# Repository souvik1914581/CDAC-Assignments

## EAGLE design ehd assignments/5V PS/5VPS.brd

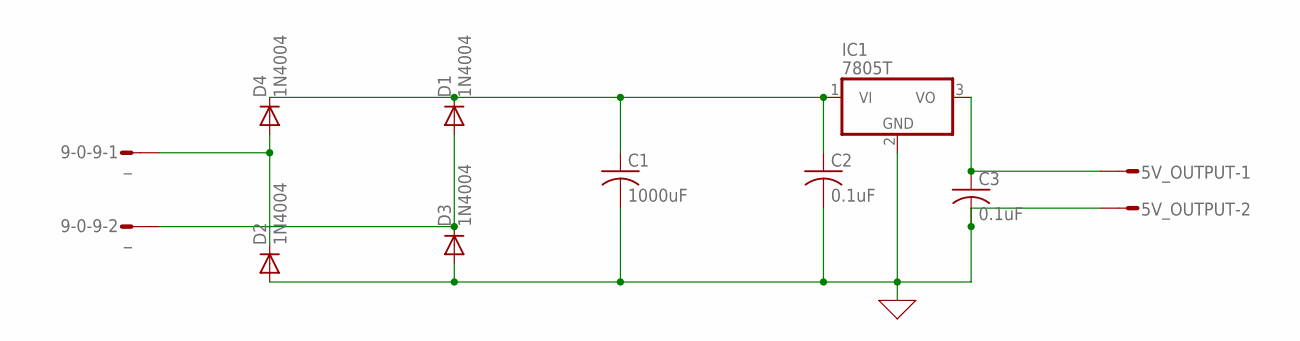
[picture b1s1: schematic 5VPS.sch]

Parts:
5V_OUTPUT: L02P
9-0-9: _; L02P
C1: 1000uF; C025-030X050
C2, C3: 0.1uF; C025-024X044
D1, D2, D3, D4: 1N4004; DO41-10
IC1: 7805T; TO220H

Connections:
0: 5V_OUTPUT.2, C1.2, C2.2, C3.2, D2.A, D3.A, IC1.2 (GND)
unnamed: 9-0-9.1, D2.C, D4.A
unnamed: C1.1, C2.1, D1.C, D4.C, IC1.1 (VI)
unnamed: 5V_OUTPUT.1, C3.1, IC1.3 (VO)
unnamed: 9-0-9.2, D1.A, D3.C

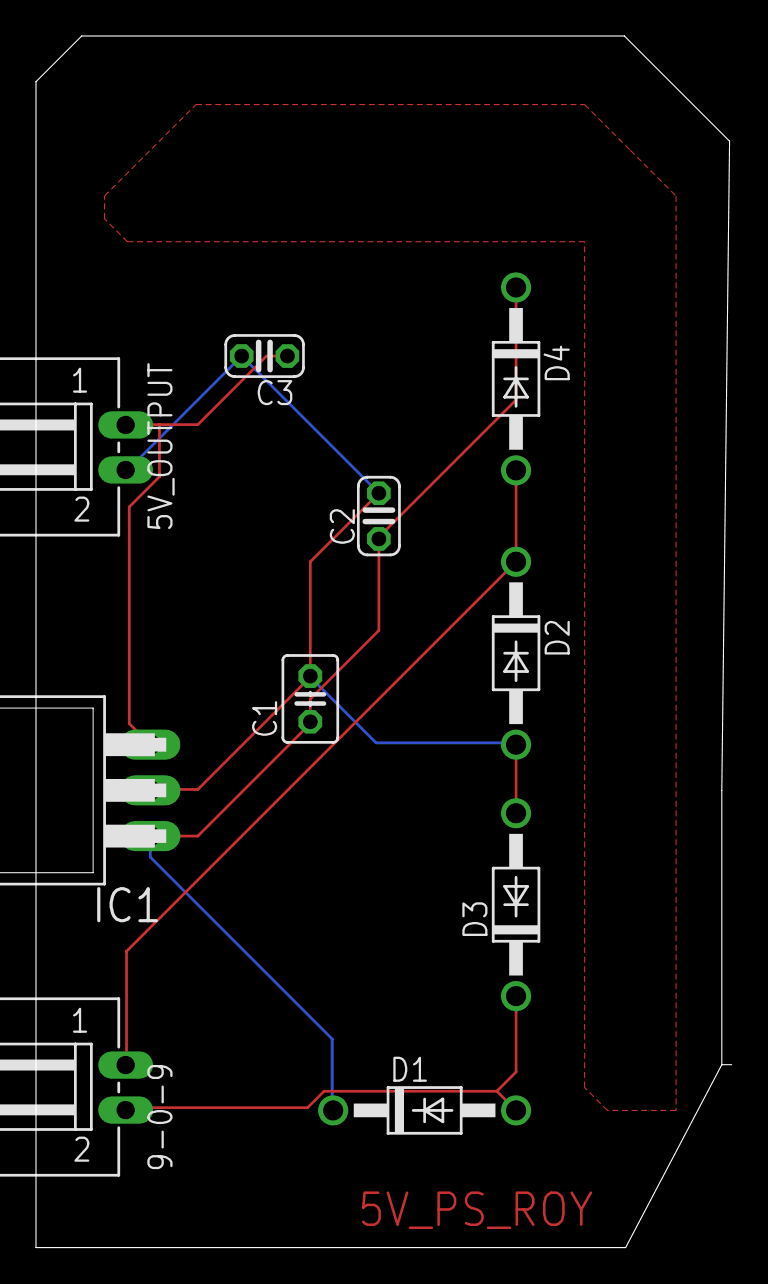
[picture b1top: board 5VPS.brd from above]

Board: 2 copper layers, 38.6 x 67.3 mm, 10 parts (0 on the bottom side), 5 nets.

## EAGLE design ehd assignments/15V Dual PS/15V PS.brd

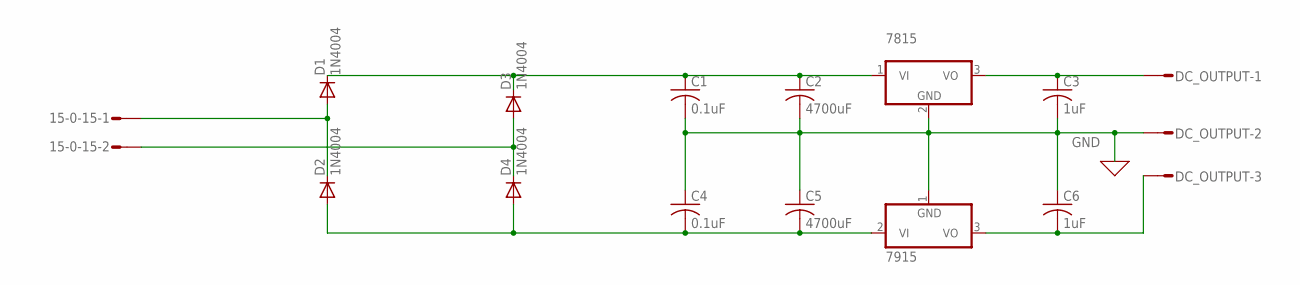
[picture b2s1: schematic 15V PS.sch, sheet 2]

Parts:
15-0-15: L02P
7815: 7815T; TO220H
7915: 7915T; TO220H
C1, C4: 0.1uF; C025-024X044
C2, C5: 4700uF; C025-024X044
C3, C6: 1uF; C025-024X044
D1, D2, D3, D4: 1N4004; DO41-10
DC_OUTPUT: L03P

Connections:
GND: 7815.2 (GND), 7915.1 (GND), C1.2, C2.2, C3.2, C4.1, C5.1, C6.1, DC_OUTPUT.2
unnamed: 15-0-15.1, D1.A, D2.C
unnamed: 15-0-15.2, D3.A, D4.C
unnamed: 7915.2 (VI), C4.2, C5.2, D2.A, D4.A
unnamed: 7815.1 (VI), C1.1, C2.1, D1.C, D3.C
unnamed: 7915.3 (VO), C6.2, DC_OUTPUT.3
unnamed: 7815.3 (VO), C3.1, DC_OUTPUT.1

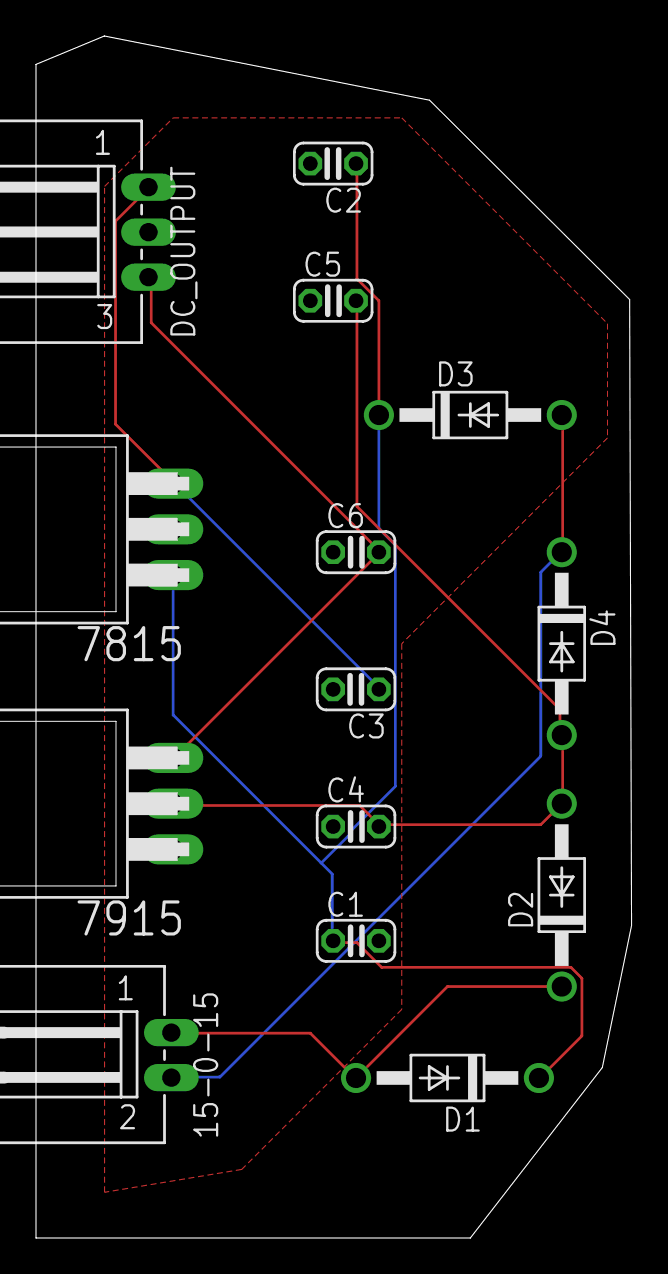
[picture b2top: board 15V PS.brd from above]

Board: 2 copper layers, 33.1 x 66.8 mm, 14 parts (0 on the bottom side), 7 nets.

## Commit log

2018-11-18 First upload of all CDAC assignments
2018-11-28 Device_Drivers assignments update
2018-11-30 Device Drivers lab exam question
2018-11-30 Device Drivers lab exam question updated
2018-12-02 Device Drivers Day5 Q2,Q3,Q4;case study updated
